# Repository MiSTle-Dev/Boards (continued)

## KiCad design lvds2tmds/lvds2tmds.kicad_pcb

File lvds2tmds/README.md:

# LVDS2TMDS

The Trion T20 FPGA used on the [Efinix T20BGA256 development
board](https://www.efinixinc.com/products-devkits-triont20.html) has
certain limitations which prevent it from directly driving a
DVI/HDMI/TMDS signal. This board plugs into the LVDS transmitter port
of that board and does the electrical conversion to TMDS.

Unlike other solutions used with Trion FPGAs this does not
do any logical translation and the signals to be fed into this
board need to have the timing required for video transmission.

[Schematic PDF](lvds2tmds_sch.pdf)
[Layout PDF](lvds2tmds_board.pdf)

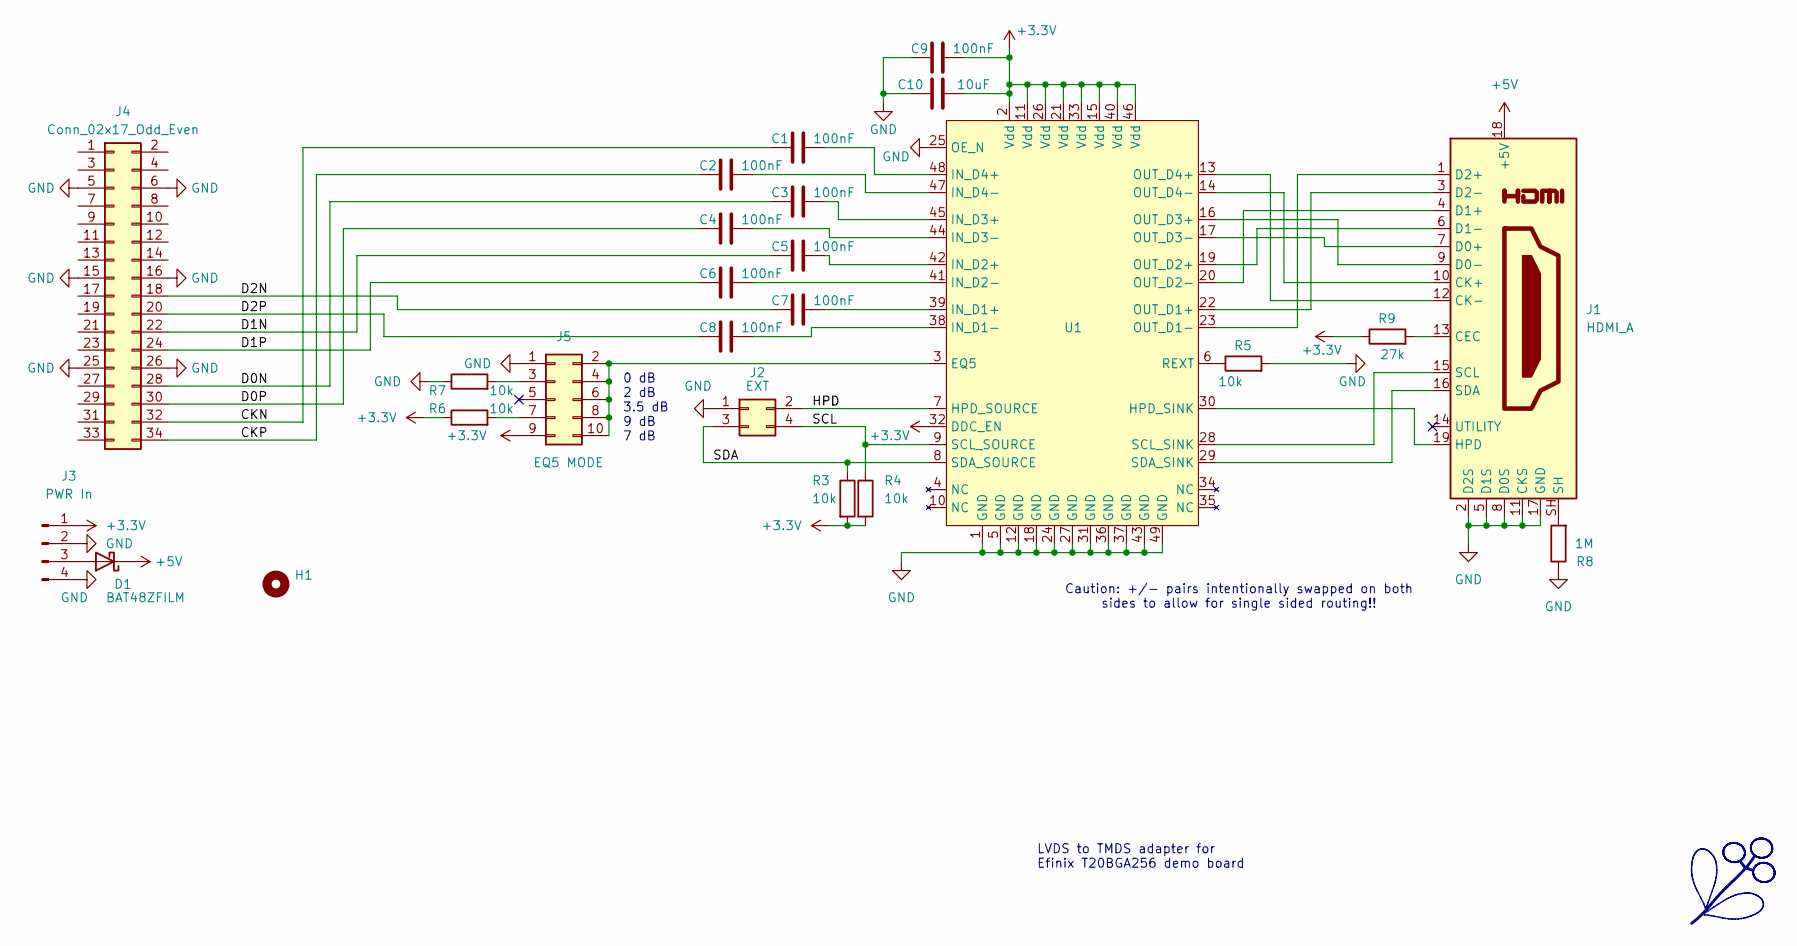
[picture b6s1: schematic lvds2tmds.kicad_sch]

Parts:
C1, C2, C3, C4, C5, C6, C7, C8, C9: 100nF; C_0805_2012Metric
C10: 10uF; C_0805_2012Metric
D1: BAT48ZFILM; D_SOD-123
H1: MountingHole; MountingHole_3.2mm_M3
J1: HDMI_A; HDMI_A_Molex_208658-1001_Horizontal
J2: EXT; PinHeader_2x02_P2.54mm_Vertical
J3: PWR In; PinHeader_1x04_P2.54mm_Vertical
J4: Conn_02x17_Odd_Even; PinSocket_2x17_P2.00mm_Vertical
J5: EQ5 MODE; PinHeader_2x05_P2.54mm_Vertical
R3, R4, R5, R6, R7: 10k; R_0805_2012Metric
R8: 1M; R_0805_2012Metric
R9: 27k; R_0805_2012Metric
U1: QFN-48-1EP_7x7mm_P0.5mm_EP5.1x5.1mm

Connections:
+3.3V: C9.2, C10.2, J3.1, J5.9, R3.2, R4.2, R6.1, R9.1, U1.2 (Vdd), U1.11 (Vdd), U1.15 (Vdd), U1.21 (Vdd), U1.26 (Vdd), U1.32 (DDC_EN), U1.33 (Vdd), U1.40 (Vdd), U1.46 (Vdd)
+5V: D1.1 (K), J1.18 (+5V)
/CKN: C1.1, J4.32
/CKP: C2.1, J4.34
/D0N: C3.1, J4.28
/D0P: C4.1, J4.30
/D1N: C5.1, J4.22
/D1P: C6.1, J4.24
/D2N: C7.1, J4.18
/D2P: C8.1, J4.20
/HPD: J2.2, U1.7 (HPD_SOURCE)
/SCL: J2.4, R4.1, U1.9 (SCL_SOURCE)
/SDA: J2.3, R3.1, U1.8 (SDA_SOURCE)
GND: C9.1, C10.1, J1.2 (D2S), J1.5 (D1S), J1.8 (D0S), J1.11 (CKS), J1.17 (GND), J2.1, J3.2, J3.4, J4.5, J4.6, J4.15, J4.16, J4.25, J4.26, J5.1, R5.2, R7.1, R8.1, U1.1 (GND), U1.5 (GND), U1.12 (GND), U1.18 (GND), U1.24 (GND), U1.25 (OE_N), U1.27 (GND), U1.31 (GND), U1.36 (GND), U1.37 (GND), U1.43 (GND), U1.49 (GND)
unnamed: D1.2 (A), J3.3
unnamed: J1.13 (CEC), R9.2
unnamed: J1.10 (CK+), U1.14 (OUT_D4-)
unnamed: J1.12 (CK-), U1.13 (OUT_D4+)
unnamed: J1.7 (D0+), U1.17 (OUT_D3-)
unnamed: J1.9 (D0-), U1.16 (OUT_D3+)
unnamed: J1.4 (D1+), U1.20 (OUT_D2-)
unnamed: J1.6 (D1-), U1.19 (OUT_D2+)
unnamed: J1.1 (D2+), U1.23 (OUT_D1-)
unnamed: J1.3 (D2-), U1.22 (OUT_D1+)
unnamed: J1.19 (HPD), U1.30 (HPD_SINK)
unnamed: J1.SH, R8.2
unnamed: J1.15 (SCL), U1.28 (SCL_SINK)
unnamed: J1.16 (SDA), U1.29 (SDA_SINK)
unnamed: J5.3, R7.2
unnamed: J5.7, R6.2
unnamed: J5.2, J5.4, J5.6, J5.8, J5.10, U1.3 (EQ5)
unnamed: C7.2, U1.39 (IN_D1+)
unnamed: C8.2, U1.38 (IN_D1-)
unnamed: C5.2, U1.42 (IN_D2+)
unnamed: C6.2, U1.41 (IN_D2-)
unnamed: C3.2, U1.45 (IN_D3+)
unnamed: C4.2, U1.44 (IN_D3-)
unnamed: C1.2, U1.48 (IN_D4+)
unnamed: C2.2, U1.47 (IN_D4-)
unnamed: R5.1, U1.6 (REXT)

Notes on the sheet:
0 dB 2 dB 3.5 dB 9 dB 7 dB
LVDS to TMDS adapter for Efinix T20BGA256 demo board
Caution: +/- pairs intentionally swapped on both sides to allow for single sided routing!!

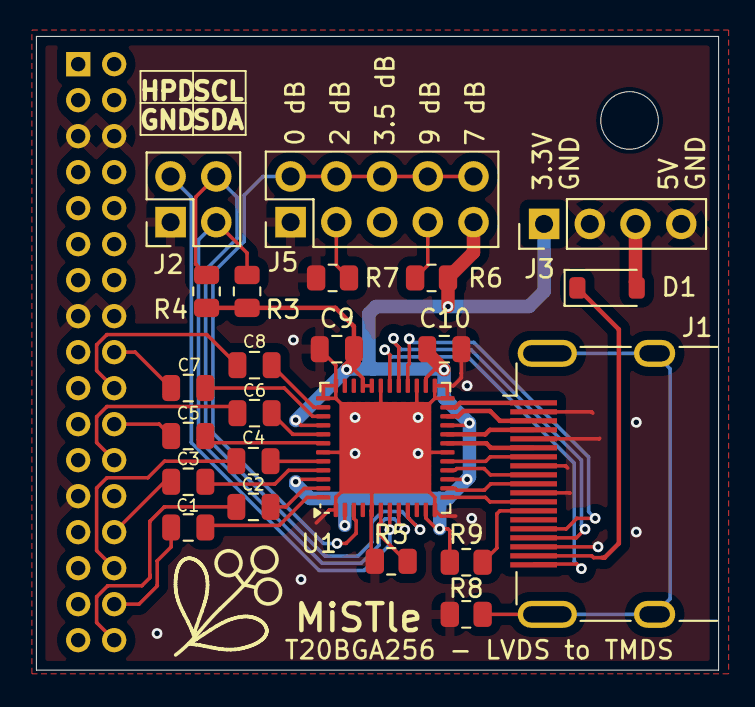
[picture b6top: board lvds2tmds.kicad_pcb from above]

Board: 2 copper layers, 37.9 x 35.2 mm, 25 parts (1 on the bottom side), 40 nets.

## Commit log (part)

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2025-08-14 More updates in dev20k
2025-08-16 dev20k update
2025-08-16 crop image
2025-08-16 remove duplicate image
2025-08-16 Update schematic pdf
2025-08-16 Update missing files
2025-08-16 Another board update
2025-08-16 Add grove connector for MIDI/UART
2025-08-18 Update board
2025-08-23 add photo pico pmod
2025-08-28 Fix dev20k schematic
2025-08-28 Update pin table
2025-08-28 Use regular jumpers for JTAG
2025-08-29 Further work on the dev20k
2025-08-30 Update mon tx/rx and spare 5 pins
2025-08-30 Update dev20k pinout
2025-08-31 First completely routed version
2025-09-01 Length match TMDS signals
2025-09-01 Adjust layer order
2025-09-01 Progress indication
2025-09-02 Dev20k LCSC part mapping
2025-09-03 Fix readme
2025-09-03 Revert overwritten contents
2025-09-03 Fix joystick connections
2025-09-03 Update netlist
2025-09-04 Update debug UART wiring
2025-09-05 Add lvds2tmds board
2025-09-05 Update board pdf
2025-09-08 Fix JLCPCB footprint offset and rotation
2025-09-08 Add preliminary JLCPCB fabrication data
2025-09-10 Add hyperram
2025-09-11 Small board cleanups
2025-09-11 Add PCB PDF
2025-09-23 More small pcb updates
2025-09-23 Update production data
2025-09-23 Fix FPGA orientation in production files
2025-09-25 Add housing from MisterNano PR #82
2025-09-29 Replace ch334u by ch334r due to availablity
2025-09-29 Add jlcpcb rendering
2025-09-29 Add production readme
2025-10-16 Shipping update
2025-10-22 Dev20k progress
2025-10-23 Report progress
2025-10-23 More progress
2025-10-28 Update state
2025-10-30 Issues
2025-11-07 Initial version of test core
2025-11-07 Fix formatting of gratitude note in README.md
2025-11-18 Update dev board state
2025-11-24 Update dev20k state
2025-11-24 Fix typos in README.md for clarity
2025-11-25 Update progress
2025-11-26 Add MiSTle logo to test core
2025-11-26 Add some instructions
2025-12-04 Inital PSRAM test
2025-12-05 Small JTAG/PSRAM fixed for test core
2026-01-11 Document removed features in README
    Added a section detailing removed features.
2026-01-11 Update README with schematic image
    Added schematic image link to README.
2026-01-11 Fix image syntax in README.md
2026-01-11 Fix image links in README.md
    Updated image links in README for clarity.
2026-01-11 Fix formatting of DB9 joystick ports in README
2026-01-11 Add new image to README.md
2026-01-11 Update README with permission and support note
    Added a note about permission and support for the project.
2026-01-11 Fix formatting in README.md
2026-01-11 Update README to clarify board origin
2026-01-11 Add images to README for better visualization
2026-01-11 Fix schematic image link in README
    Updated image link for schematic in README.
2026-01-11 Fix image markdown syntax in README.md
2026-01-12 MISTle jtag testcode
2026-01-17 Update PCB link to KiCanvas format
2026-01-17 Update README with images and PCB link
    Added images and KiCanvas link to README.
2026-01-17 Replace Schematic2 image with USB Hub diagram
2026-01-19 Update README with feature details
2026-01-19 Replace PCB image from JPG to PNG format
2026-01-19 Fix image file extension from .png to .PNG
2026-01-20 Update README with improved feature descriptions
    Corrected formatting and clarified the alternative core loading feature description.
2026-01-20 Fix formatting in README.md for new features section
2026-01-21 Aktualisieren von README.md
2026-01-22 Revise credits formatting in README
    Updated credits section in README.md
2026-01-23 Update PCB images in README
    Replaced images in README with updated PCB images.
2026-01-24 Update README to emphasize work in progress status
2026-01-24 Update work in progress notice in README
    Combine warning about work in progress into a single line.
2026-01-24 Fix formatting of warning message in README
2026-01-24 Remove MIDI image from README
    Removed one MIDI image from the README.
2026-01-24 Update README to reflect feature removals
2026-01-24 Fix MIDI description formatting in README
    Corrected formatting for MIDI feature description in README.
2026-01-24 Fix formatting of MIDI feature description in README
2026-01-24 Improve formatting of MIDI feature in README
    Reformat MIDI feature description for clarity.
2026-01-26 Rename Review Notes.md to Review_Notes.md
2026-01-30 Aktualisieren von Review_Notes.md
2026-02-23 Update README to remove USB-C Thumbstick reference
    Removed mention of alternative core loading from USB-C Thumbstick.
2026-02-25 Update production status in README
2026-03-04 Update README to remove review notes
    Removed review notes section from README.
2026-03-13 Create x
2026-03-13 Update README to reflect current project status
    Removed note indicating that the shield is a work in progress.
2026-03-27 Add console hub
2026-03-27 Cleanup image
2026-04-07 WIP: GW3A LV20 LQ144 development board
2026-04-12 Update README with JTAG and MIDI information
    Added instructions for JTAG soldering and clarified MIDI usage.
2026-04-12 readme
2026-04-13 GW3A-LV20 readme
2026-04-15 Update gw3a dev board
2026-04-24 Update README with DB9 Port and JTAG details
2026-04-25 Remove BOM image from README
    Removed BOM image from README.
2026-05-06 Update gw3a 20 dev board
2026-05-06 Fix typo
2026-05-06 resize board
2026-05-07 Link to new boards
2026-05-08 Update gw3a board
2026-05-22 Update mistle-gw3a board for rp2350
2026-05-22 Test blender rendering
2026-05-25 Updated render
2026-05-25 Add blender file
2026-06-01 Add expansion connector
2026-06-12 Document progress
2026-06-14 Adjust orientation of L2 in the JLC production data. Cudos to JLC for pointing that out
